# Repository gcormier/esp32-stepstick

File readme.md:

# ESP32-STEPSTICK

Control some stepstick-style stepper drivers with an ESP32.

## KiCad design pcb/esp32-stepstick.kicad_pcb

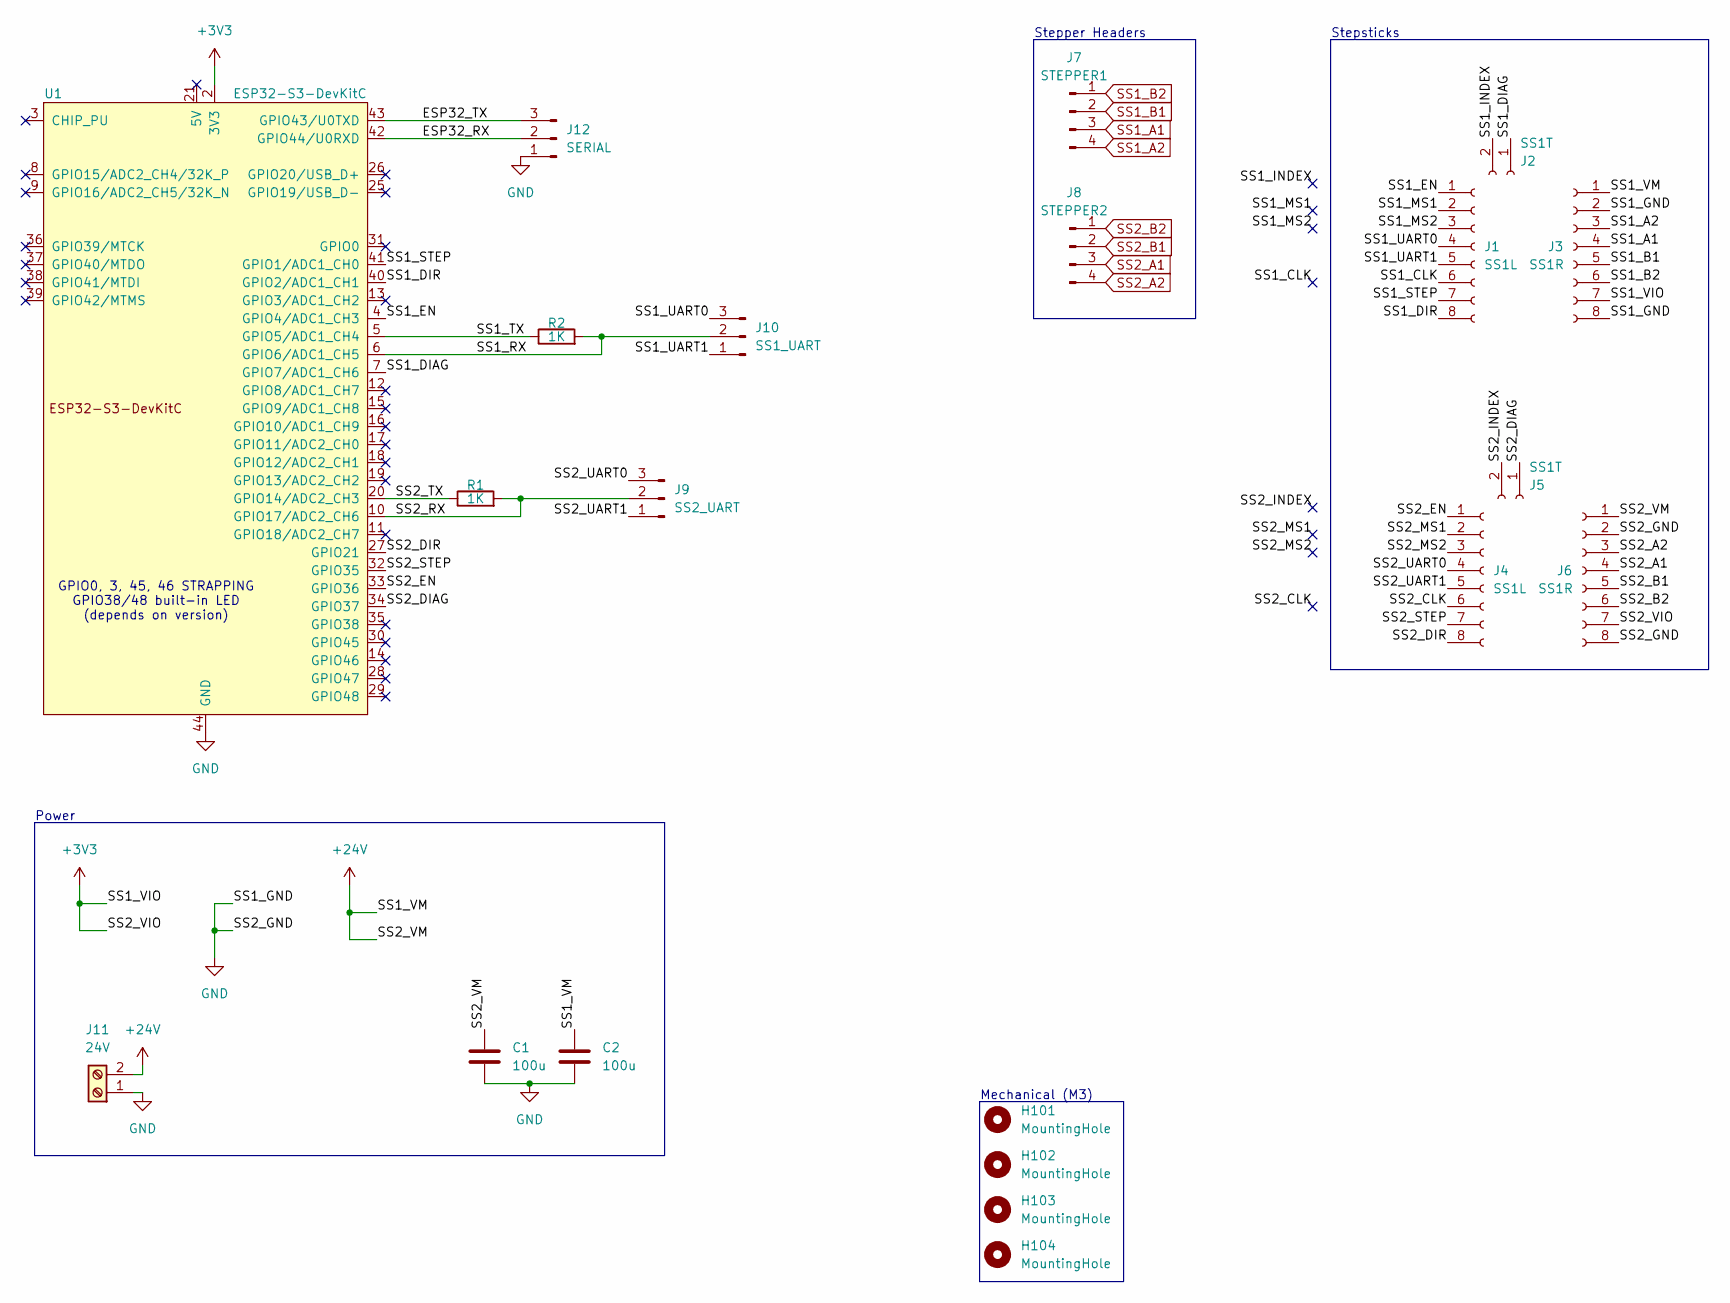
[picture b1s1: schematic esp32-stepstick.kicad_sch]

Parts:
C1, C2: 100u; C_Radial_D10.0mm_H12.5mm_P5.00mm
H101, H102, H103, H104: MountingHole; MountingHole_3.2mm_M3_DIN965
J1, J4: SS1L; PinSocket_1x08_P2.54mm_Vertical
J2, J5: SS1T; PinSocket_1x02_P2.54mm_Vertical
J3, J6: SS1R; PinSocket_1x08_P2.54mm_Vertical
J7: STEPPER1; PhoenixContact_MC_1,5_4-G-3.81_1x04_P3.81mm_Horizontal
J8: STEPPER2; PhoenixContact_MC_1,5_4-G-3.81_1x04_P3.81mm_Horizontal
J9: SS2_UART; PinHeader_1x03_P2.54mm_Vertical
J10: SS1_UART; PinHeader_1x03_P2.54mm_Vertical
J11: 24V; TerminalBlock_Phoenix_MKDS-1,5-2-5.08_1x02_P5.08mm_Horizont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
J12: SERIAL; PinHeader_1x03_P2.54mm_Vertical
R1, R2: 1K; R_Axial_DIN0309_L9.0mm_D3.2mm_P15.24mm_Horizontal
U1: ESP32-S3-DevKitC

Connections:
+3V3: J3.7, J6.7, U1.1 (3V3), U1.2 (3V3)
+24V: C1.1, C2.1, J3.1, J6.1, J11.2
/ESP32_RX: J12.2, U1.42 (GPIO44/U0RXD)
/ESP32_TX: J12.3, U1.43 (GPIO43/U0TXD)
/SS1_CLK: J1.6
/SS1_DIAG: J2.1, U1.7 (GPIO7/ADC1_CH6)
/SS1_DIR: J1.8, U1.40 (GPIO2/ADC1_CH1)
/SS1_EN: J1.1, U1.4 (GPIO4/ADC1_CH3)
/SS1_INDEX: J2.2
/SS1_MS1: J1.2
/SS1_MS2: J1.3
/SS1_RX: J10.2, R2.2, U1.6 (GPIO6/ADC1_CH5)
/SS1_STEP: J1.7, U1.41 (GPIO1/ADC1_CH0)
/SS1_TX: R2.1, U1.5 (GPIO5/ADC1_CH4)
/SS1_UART0: J1.4, J10.3
/SS1_UART1: J1.5, J10.1
/SS2_CLK: J4.6
/SS2_DIAG: J5.1, U1.34 (GPIO37)
/SS2_DIR: J4.8, U1.27 (GPIO21)
/SS2_EN: J4.1, U1.33 (GPIO36)
/SS2_INDEX: J5.2
/SS2_MS1: J4.2
/SS2_MS2: J4.3
/SS2_RX: J9.2, R1.2, U1.10 (GPIO17/ADC2_CH6)
/SS2_STEP: J4.7, U1.32 (GPIO35)
/SS2_TX: R1.1, U1.20 (GPIO14/ADC2_CH3)
/SS2_UART0: J4.4, J9.3
/SS2_UART1: J4.5, J9.1
GND: C1.2, C2.2, J3.2, J3.8, J6.2, J6.8, J11.1, J12.1, U1.22 (GND), U1.23 (GND), U1.24 (GND), U1.44 (GND)
SS1_A1: J3.4, J7.3
SS1_A2: J3.3, J7.4
SS1_B1: J3.5, J7.2
SS1_B2: J3.6, J7.1
SS2_A1: J6.4, J8.3
SS2_A2: J6.3, J8.4
SS2_B1: J6.5, J8.2
SS2_B2: J6.6, J8.1

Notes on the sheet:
Power
GPIO0, 3, 45, 46 STRAPPING GPIO38/48 built-in LED (depends on version)
Stepsticks
Stepper Headers
Mechanical (M3)

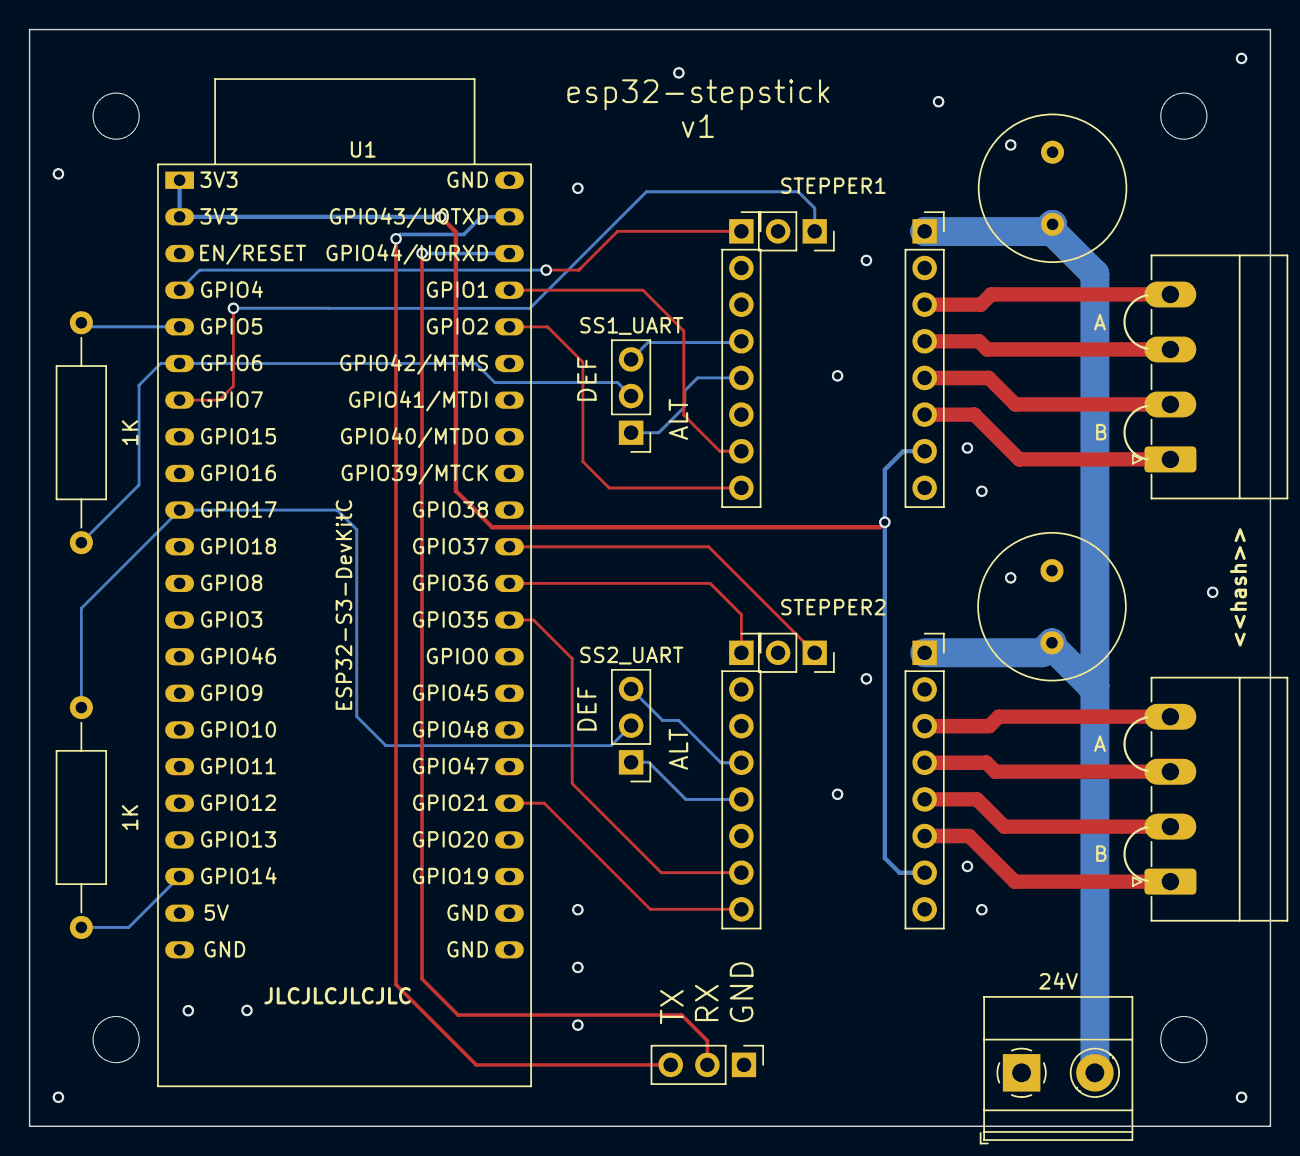
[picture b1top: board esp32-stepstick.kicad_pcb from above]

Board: 4 copper layers, 86.0 x 76.0 mm, 21 parts (0 on the bottom side), 29 nets.

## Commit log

2024-12-29 basic code
2024-12-29 homing and movement test working
2024-12-29 final tweaks to max speed
2024-12-29 bit of sanity
